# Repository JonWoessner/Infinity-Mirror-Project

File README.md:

Neopixel Infinity Mirror using ESP32c3 for high school electronics, engineering, or computer science courses. Features a small 3D printed case, PCB to solder, and uses Adafruit's Neopixel library for control.

----
Feb 20th Purdue ETTE PD

If you're here for the PD, welcome! We will take care of installing and setting up arduino first thing. If you can, install the Arduino IDE by going to this link: https://www.arduino.cc/en/software/

Once installed, we will add a board manager for the microcontroller we will use.  You will need to copy the link below into the Arduino IDE in the Preferences section: 

https://espressif.github.io/arduino-esp32/package_esp32_index.json

From there, we will add the "esp32 by Espressif Systems" in our boards manager, by searching for "esp32".

Then, we will add the Adafruit Neopixel Library from the library manager.

---- 

New home for the infinity mirror project. need to move over and format/clean materials from other folders.
Here's the initial project structure: 
readme.md
-pictures and videos
-hardware
	-3D model
	-PCB
	-old laser files
	pdf/dwg/svg of acrylic parts
	bill of materials.md
-example code
	-folder with PIO config
	-folders with Arduino ino's
	list of Arduino pref url.txt
-documentation
	hardware assembly
	bill of materials
	software how tos
	troubleshooting
	teaching/curricular notes

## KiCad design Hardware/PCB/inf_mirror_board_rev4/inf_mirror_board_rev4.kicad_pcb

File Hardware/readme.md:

This folder will contain folders for hardware source files, then the following: 
- stls of printed parts
- pdf/svg/whatnot for the lasered acrylic parts
- zip file of most recent pcb revision
- bill of materials with links and aprox costs

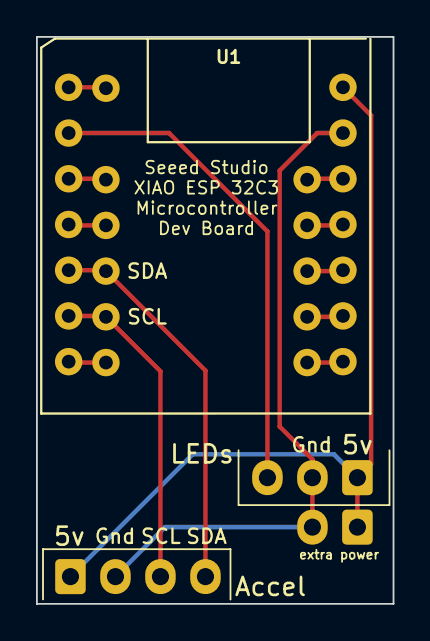
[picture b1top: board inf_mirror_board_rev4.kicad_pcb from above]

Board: 2 copper layers, 19.8 x 31.5 mm, 3 parts (0 on the bottom side), 5 nets.

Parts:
Accel: Accel; JST_EH_B4B-EH-A_1x04_P2.50mm_Vertical
LEDs: led_strip; JST_EH_B3B-EH-A_1x03_P2.50mm_Vertical
U1: MOUDLE-SEEEDUINO-XIAO-ESP32C3; MOUDLE14P-SMD-2.54-21X17.8MM

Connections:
unnamed: LEDs.3 (Din), U1.2 (PA4_A1_D1)
unnamed: Accel.4 (SDA), U1.5 (PA8_A4_D4_SDA)
unnamed: Accel.3 (SCL), U1.6 (PA9_A5_D5_SCL)
unnamed: Accel.2 (Gnd), LEDs.2 (Gnd), U1.13 (GND)
unnamed: Accel.1 (Vcc), LEDs.1 (vcc), U1.14 (5V)

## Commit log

2026-02-20 Add files via upload
    Initial commit!
